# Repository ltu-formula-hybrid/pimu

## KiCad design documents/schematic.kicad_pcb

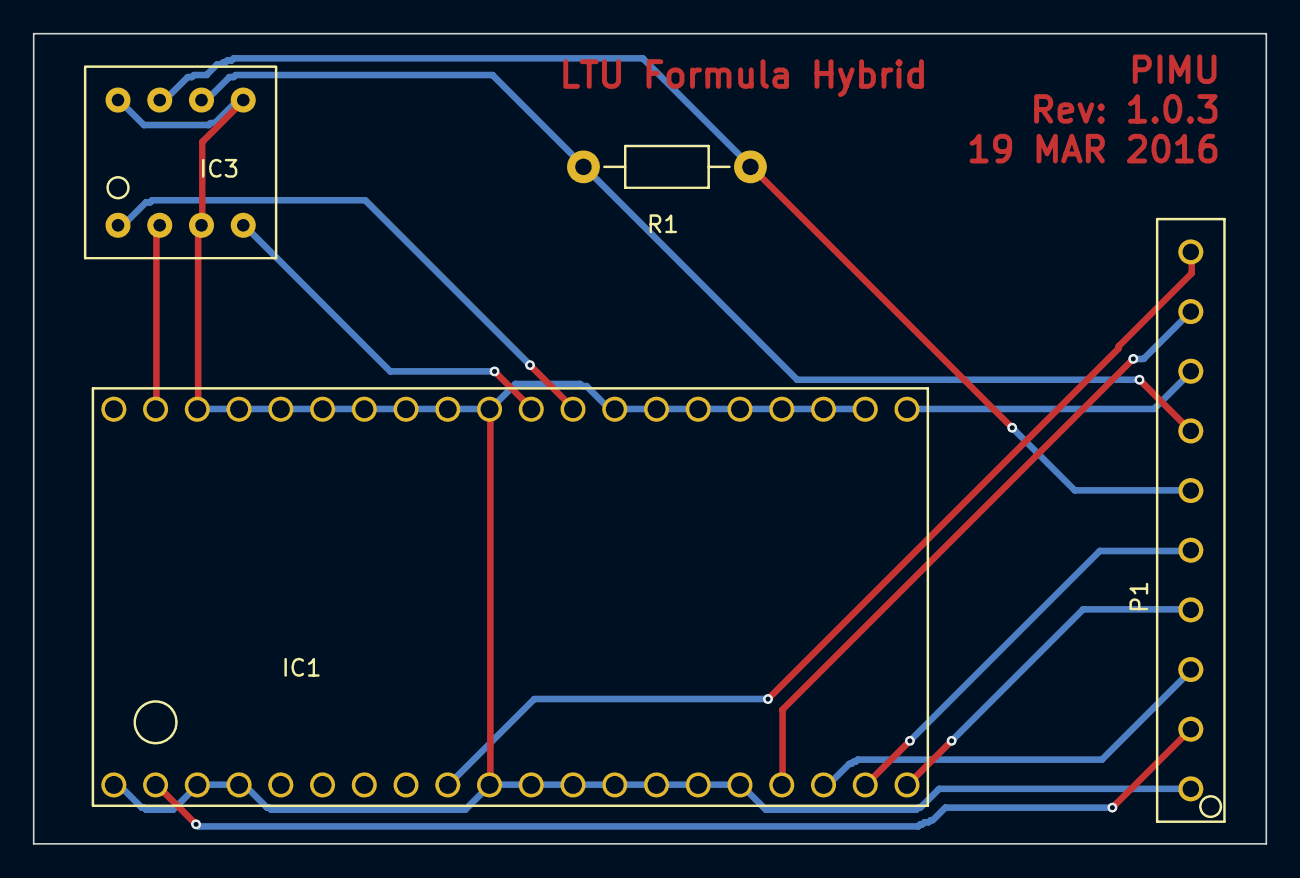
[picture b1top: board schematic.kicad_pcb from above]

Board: 2 copper layers, 75.0 x 49.3 mm, 4 parts (0 on the bottom side), 13 nets.

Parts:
IC1: LPC1768
IC3: MCP2551; MCP2551-ESN
P1: CONN_01X10; CONN_01X10_CUST
R1: 120; Resistor_Horizontal_RM10mm

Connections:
10VDC: IC1.2, P1.2
CANH: IC3.7, P1.6, R1.1
CANL: IC3.6, P1.7, R1.2
EM_MC: IC1.18, P1.3
FAN_CTRL: IC1.17, P1.9
GND: IC1.1, IC1.3, IC1.4, IC1.10, IC1.11, IC1.12, IC1.13, IC1.14, IC1.15, IC1.16, IC1.22, IC1.23, IC1.24, IC1.25, IC1.26, IC1.27, IC1.28, IC1.31, IC1.32, IC1.33, IC1.34, IC1.35, IC1.36, IC1.37, IC1.38, IC3.3, IC3.5, IC3.8, P1.1
MC_CTRL: IC1.21, P1.8
unnamed: IC1.29, IC3.1
unnamed: IC1.30, IC3.4
unnamed: IC1.39, IC3.2
STARTER_SIG: IC1.9, P1.10
TP_CH1: IC1.20, P1.4
TP_CH2: IC1.19, P1.5

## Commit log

2015-11-03 Bringing over example project from DAS
2015-11-03 Fixed missing newline
2015-11-04 Squashed 'components/' content from commit 1f79638
    git-subtree-dir: components
    git-subtree-split: 1f7963839451faed4b067d44112e60d6c893831b
2015-12-21 initial test code for pimu control
    test code for serial communication between pololu and PIMU
2015-12-21 initial test code changes
2016-01-09 test code
    update
2016-01-09 Working code for TPS feedback
2016-01-09 Throttle body idles
2016-01-09 Better than yesterday
2016-01-13 Kinda working
2016-01-30 Progress with TbCtrl
2016-02-03 Making changes
2016-02-16 Added docs and updated code
2016-02-20 Working CAN testing
2016-02-25 yasaCut off [FIX]
    fixed yasaCutOff code
2016-03-15 Documentation and PCB design
2016-03-26 With RAMP UP algorithm
    implemented ramp up code for yasa
    [NOTE]
    0.01 corresponds to about a second delay. 0.005 corresponds to 3 second
    delay.
2016-04-02 With Backward and forward funct
2016-04-16 With PWM IN libs
    not actually needed
